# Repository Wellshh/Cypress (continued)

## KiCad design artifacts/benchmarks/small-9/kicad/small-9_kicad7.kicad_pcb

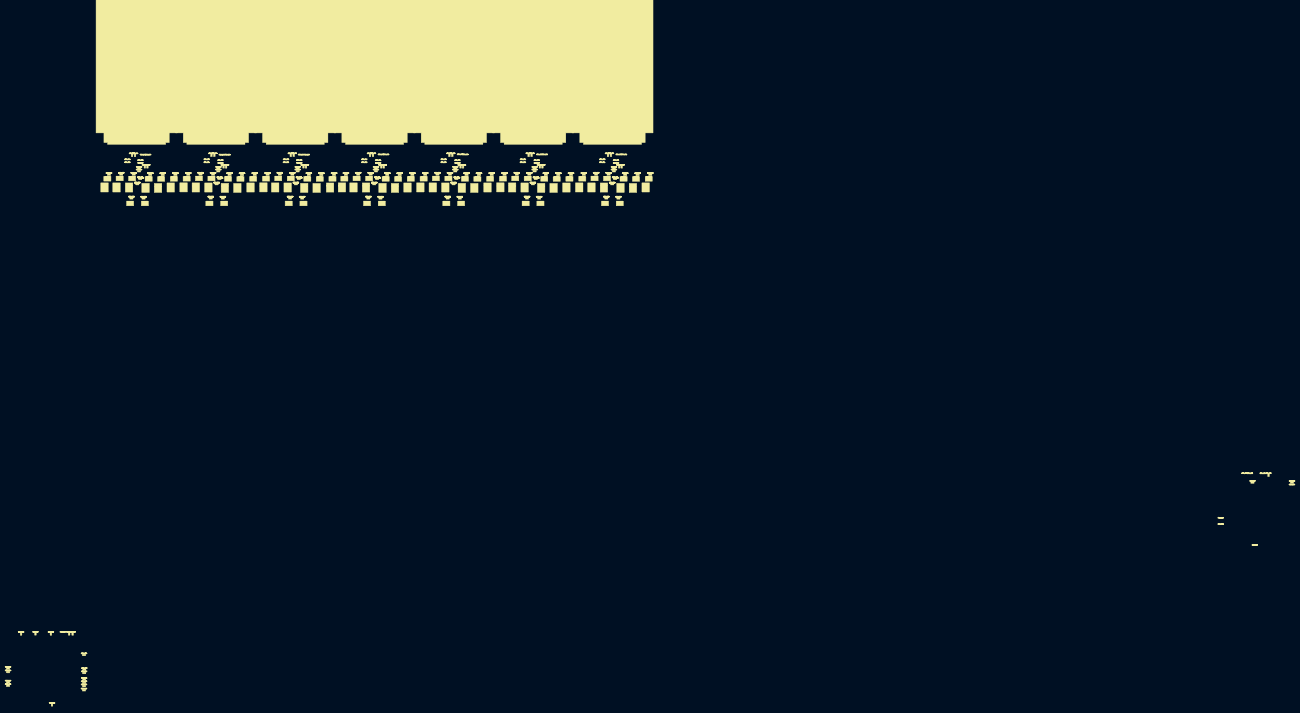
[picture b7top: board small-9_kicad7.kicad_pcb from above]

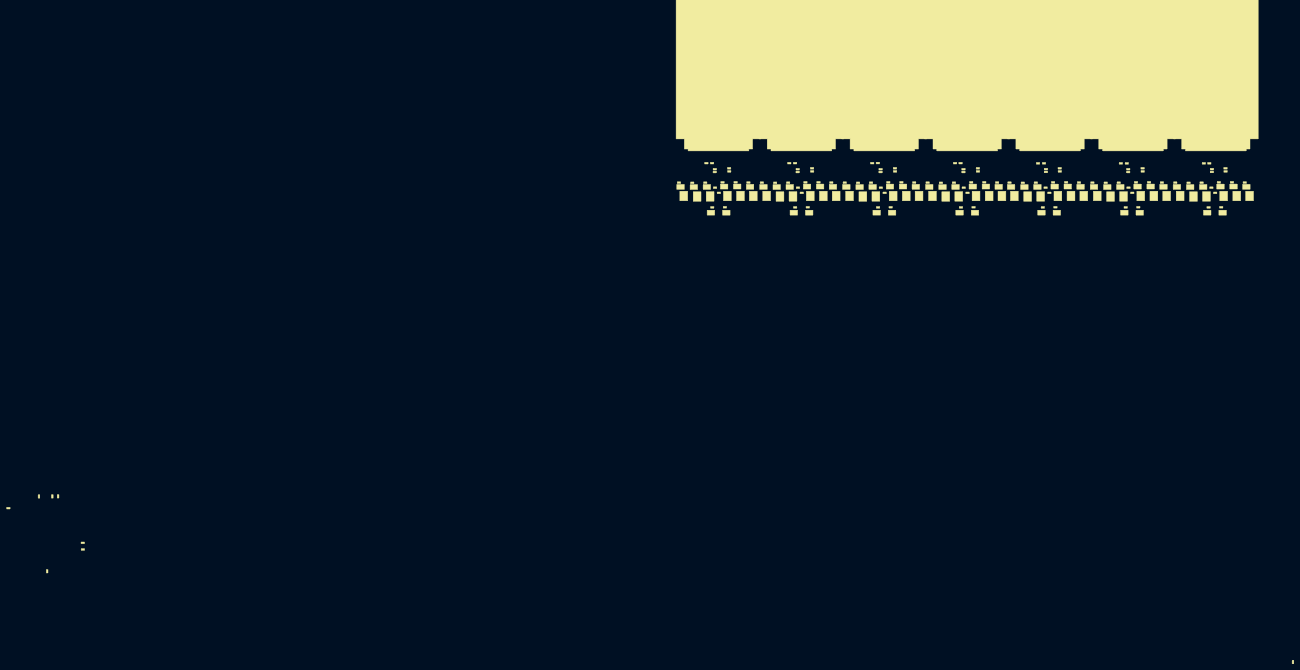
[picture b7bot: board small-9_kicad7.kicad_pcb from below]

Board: 2 copper layers, 476 parts (232 on the bottom side), 253 nets, no tracks yet.

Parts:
COMP_232: COMP_232; 320-2241-000
COMP_233: COMP_233; 320-2241-000
COMP_234: COMP_234; 320-2241-000
COMP_235: COMP_235; 320-2241-000
COMP_236: COMP_236; 320-2241-000
COMP_237: COMP_237; 320-2241-000
COMP_238: COMP_238; 320-2241-000
COMP_239: COMP_239; 320-2241-000
COMP_240: COMP_240; 320-2241-000
COMP_241: COMP_241; 320-2241-000
COMP_242: COMP_242; 320-2241-000
COMP_243: COMP_243; 320-2241-000
COMP_244: COMP_244; 320-2241-000
COMP_245: COMP_245; 320-2241-000
COMP_469: COMP_469; 032-2145-000
COMP_470: COMP_470; 032-2145-000
COMP_480: COMP_480; 032-2145-000
COMP_481: COMP_481; 032-2145-000
COMP_482: COMP_482; 032-2145-000
COMP_483: COMP_483; 032-2145-000
COMP_484: COMP_484; 032-2145-000
COMP_485: COMP_485; 032-2145-000
COMP_486: COMP_486; 032-2145-000
COMP_487: COMP_487; 032-2145-000
COMP_488: COMP_488; 032-2145-000
COMP_489: COMP_489; 032-2145-000
COMP_490: COMP_490; 032-2145-000
COMP_491: COMP_491; 032-2145-000
COMP_492: COMP_492; 032-2145-000
COMP_493: COMP_493; 032-2145-000
COMP_494: COMP_494; 032-2145-000
COMP_495: COMP_495; 032-2145-000
COMP_496: COMP_496; 032-2145-000
COMP_497: COMP_497; 032-2145-000
COMP_498: COMP_498; 032-2145-000
COMP_606: COMP_606; 032-2145-000
COMP_607: COMP_607; 032-2145-000
COMP_608: COMP_608; 032-2145-000
COMP_609: COMP_609; 032-2145-000
COMP_610: COMP_610; 032-2145-000
COMP_611: COMP_611; 032-2145-000
COMP_612: COMP_612; 032-2145-000
COMP_613: COMP_613; 032-2145-000
COMP_614: COMP_614; 032-2145-000
COMP_615: COMP_615; 032-2145-000
COMP_616: COMP_616; 032-2145-000
COMP_617: COMP_617; 032-2145-000
COMP_618: COMP_618; 032-2145-000
COMP_619: COMP_619; 032-2145-000
COMP_620: COMP_620; 032-2145-000
COMP_621: COMP_621; 032-2145-000
COMP_622: COMP_622; 032-2145-000
COMP_623: COMP_623; 032-2145-000
COMP_624: COMP_624; 032-2145-000
COMP_625: COMP_625; 032-2145-000
COMP_626: COMP_626; 032-2145-000
COMP_627: COMP_627; 032-2145-000
COMP_628: COMP_628; 032-2145-000
COMP_629: COMP_629; 032-2145-000
COMP_630: COMP_630; 032-2145-000
COMP_631: COMP_631; 032-2145-000
COMP_632: COMP_632; 032-2145-000
COMP_633: COMP_633; 032-2145-000
COMP_634: COMP_634; 032-2145-000
COMP_635: COMP_635; 032-2145-000
COMP_636: COMP_636; 032-2145-000
COMP_637: COMP_637; 032-2145-000
COMP_638: COMP_638; 032-2145-000
COMP_639: COMP_639; 032-2145-000
COMP_640: COMP_640; 032-2145-000
COMP_641: COMP_641; 032-2145-000
COMP_642: COMP_642; 032-2145-000
COMP_643: COMP_643; 032-2145-000
COMP_644: COMP_644; 032-2145-000
COMP_645: COMP_645; 032-2145-000
COMP_646: COMP_646; 032-2145-000
COMP_647: COMP_647; 032-2145-000
COMP_648: COMP_648; 032-2145-000
COMP_649: COMP_649; 032-2145-000
COMP_650: COMP_650; 032-2145-000
COMP_651: COMP_651; 032-2145-000
COMP_652: COMP_652; 032-2145-000
COMP_653: COMP_653; 032-2145-000
COMP_654: COMP_654; 032-2145-000
COMP_655: COMP_655; 032-2145-000
COMP_656: COMP_656; 032-2145-000
COMP_657: COMP_657; 032-2145-000
COMP_658: COMP_658; 032-2145-000
COMP_659: COMP_659; 032-2145-000
COMP_660: COMP_660; 032-2145-000
COMP_661: COMP_661; 032-2145-000
COMP_662: COMP_662; 032-2145-000
COMP_663: COMP_663; 032-2145-000
COMP_664: COMP_664; 032-2145-000
COMP_665: COMP_665; 032-2145-000
COMP_666: COMP_666; 032-2145-000
COMP_667: COMP_667; 032-2145-000
COMP_668: COMP_668; 032-2145-000
COMP_669: COMP_669; 032-2145-000
COMP_670: COMP_670; 032-2145-000
COMP_671: COMP_671; 032-2145-000
COMP_672: COMP_672; 032-2145-000
COMP_673: COMP_673; 032-2145-000
COMP_674: COMP_674; 032-2145-000
COMP_675: COMP_675; 032-2145-000
COMP_676: COMP_676; 032-2145-000
COMP_677: COMP_677; 032-2145-000
COMP_678: COMP_678; 032-2145-000
COMP_679: COMP_679; 032-2145-000
COMP_680: COMP_680; 032-2145-000
COMP_681: COMP_681; 032-2145-000
COMP_682: COMP_682; 032-2145-000
COMP_683: COMP_683; 032-2145-000
COMP_684: COMP_684; 032-2145-000
COMP_685: COMP_685; 032-2145-000
COMP_686: COMP_686; 032-2145-000
COMP_687: COMP_687; 032-2145-000
COMP_688: COMP_688; 032-2145-000
COMP_689: COMP_689; 032-2145-000
COMP_690: COMP_690; 032-2145-000
COMP_691: COMP_691; 032-2145-000
COMP_692: COMP_692; 032-2145-000
COMP_717: COMP_717; 032-2145-000
COMP_724: COMP_724; 032-2145-000
COMP_725: COMP_725; 032-2145-000
COMP_726: COMP_726; 032-2145-000
COMP_984: COMP_984; 080-2248-000
COMP_985: COMP_985; 080-2248-000
COMP_988: COMP_988; 080-2248-000
COMP_989: COMP_989; 080-2248-000
COMP_990: COMP_990; 080-2248-000
COMP_991: COMP_991; 080-2248-000
COMP_992: COMP_992; 080-2248-000
COMP_993: COMP_993; 080-2248-000
COMP_994: COMP_994; 080-2248-000
COMP_995: COMP_995; 080-2248-000
COMP_996: COMP_996; 080-2248-000
COMP_997: COMP_997; 080-2248-000
COMP_998: COMP_998; 080-2248-000
COMP_999: COMP_999; 080-2248-000
COMP_1016: COMP_1016; 130-1487-000
COMP_1017: COMP_1017; 130-1487-000
COMP_1102: COMP_1102; 130-1487-000
COMP_1103: COMP_1103; 130-1487-000
COMP_1104: COMP_1104; 130-1487-000
COMP_1105: COMP_1105; 130-1487-000
COMP_1106: COMP_1106; 130-1487-000
COMP_1107: COMP_1107; 130-1487-000
COMP_1108: COMP_1108; 130-1487-000
COMP_1109: COMP_1109; 130-1487-000
COMP_1110: COMP_1110; 130-1487-000
COMP_1111: COMP_1111; 130-1487-000
COMP_1112: COMP_1112; 130-1487-000
COMP_1113: COMP_1113; 130-1487-000
COMP_1114: COMP_1114; 130-1487-000
COMP_1115: COMP_1115; 130-1487-000
COMP_1116: COMP_1116; 130-1487-000
COMP_1117: COMP_1117; 130-1487-000
COMP_1118: COMP_1118; 130-1487-000
COMP_1119: COMP_1119; 130-1487-000
COMP_1120: COMP_1120; 130-1487-000
COMP_1121: COMP_1121; 130-1487-000
COMP_1122: COMP_1122; 130-1487-000
COMP_1123: COMP_1123; 130-1487-000
COMP_1124: COMP_1124; 130-1487-000
COMP_1125: COMP_1125; 130-1487-000
COMP_1126: COMP_1126; 130-1487-000
COMP_1127: COMP_1127; 130-1487-000
COMP_1128: COMP_1128; 130-1487-000
COMP_1129: COMP_1129; 130-1487-000
COMP_1130: COMP_1130; 130-1487-000
COMP_1131: COMP_1131; 130-1487-000
COMP_1132: COMP_1132; 130-1487-000
COMP_1133: COMP_1133; 130-1487-000
COMP_1134: COMP_1134; 130-1487-000
COMP_1135: COMP_1135; 130-1487-000
COMP_1136: COMP_1136; 130-1487-000
COMP_1137: COMP_1137; 130-1487-000
COMP_1138: COMP_1138; 130-1487-000
COMP_1139: COMP_1139; 130-1487-000
COMP_1140: COMP_1140; 130-1487-000
COMP_1141: COMP_1141; 130-1487-000
COMP_1142: COMP_1142; 130-1487-000
COMP_1143: COMP_1143; 130-1487-000
COMP_1144: COMP_1144; 130-1487-000
COMP_1145: COMP_1145; 130-1487-000
COMP_1146: COMP_1146; 130-1487-000
COMP_1147: COMP_1147; 130-1487-000
COMP_1148: COMP_1148; 130-1487-000
COMP_1149: COMP_1149; 130-1487-000
COMP_1150: COMP_1150; 130-1487-000
COMP_1151: COMP_1151; 130-1487-000
COMP_1152: COMP_1152; 130-1487-000
COMP_1153: COMP_1153; 130-1487-000
COMP_1154: COMP_1154; 130-1487-000
COMP_1155: COMP_1155; 130-1487-000
COMP_1156: COMP_1156; 130-1487-000
COMP_1157: COMP_1157; 130-1487-000
COMP_1158: COMP_1158; 130-1487-000
COMP_1159: COMP_1159; 130-1487-000
COMP_1160: COMP_1160; 130-1487-000
COMP_1161: COMP_1161; 130-1487-000
COMP_1162: COMP_1162; 130-1487-000
COMP_1163: COMP_1163; 130-1487-000
COMP_1164: COMP_1164; 130-1487-000
COMP_1165: COMP_1165; 130-1487-000
COMP_1166: COMP_1166; 130-1487-000
COMP_1167: COMP_1167; 130-1487-000
COMP_1168: COMP_1168; 130-1487-000
COMP_1169: COMP_1169; 130-1487-000
COMP_1170: COMP_1170; 130-1487-000
COMP_1171: COMP_1171; 130-1487-000
COMP_1172: COMP_1172; 130-1487-000
COMP_1173: COMP_1173; 130-1487-000
COMP_1174: COMP_1174; 130-1487-000
COMP_1175: COMP_1175; 130-1487-000
COMP_1176: COMP_1176; 130-1487-000
COMP_1177: COMP_1177; 130-1487-000
COMP_1178: COMP_1178; 130-1487-000
COMP_1179: COMP_1179; 130-1487-000
COMP_1180: COMP_1180; 130-1487-000
COMP_1202: COMP_1202; 130-1487-000
COMP_1203: COMP_1203; 130-1487-000
COMP_1204: COMP_1204; 130-1487-000
COMP_2407: COMP_2407; 032-0863-000
COMP_2473: COMP_2473; 195-0004-000
COMP_2474: COMP_2474; 195-0004-000
COMP_2475: COMP_2475; 195-0004-000
COMP_2477: COMP_2477; 195-0004-000
COMP_2478: COMP_2478; 195-0004-000
COMP_2479: COMP_2479; 195-0004-000
COMP_2480: COMP_2480; 195-0004-000
COMP_2481: COMP_2481; 195-0004-000
COMP_2482: COMP_2482; 195-0004-000
COMP_2483: COMP_2483; 195-0004-000
COMP_2484: COMP_2484; 195-0004-000
COMP_2485: COMP_2485; 195-0004-000
COMP_2486: COMP_2486; 195-0004-000
COMP_2487: COMP_2487; 195-0004-000
COMP_2488: COMP_2488; 195-0004-000
COMP_2489: COMP_2489; 195-0004-000
COMP_2490: COMP_2490; 195-0004-000
COMP_2491: COMP_2491; 195-0004-000
COMP_2492: COMP_2492; 195-0004-000
COMP_2493: COMP_2493; 195-0004-000
COMP_2494: COMP_2494; 195-0004-000
COMP_2495: COMP_2495; 195-0004-000
COMP_2496: COMP_2496; 195-0004-000
COMP_2497: COMP_2497; 195-0004-000
COMP_2498: COMP_2498; 195-0004-000
COMP_2499: COMP_2499; 195-0004-000
COMP_2500: COMP_2500; 195-0004-000
COMP_2501: COMP_2501; 195-0004-000
COMP_2502: COMP_2502; 195-0004-000
COMP_2503: COMP_2503; 195-0004-000
COMP_2504: COMP_2504; 195-0004-000
COMP_2505: COMP_2505; 195-0004-000
COMP_2506: COMP_2506; 195-0004-000
COMP_2507: COMP_2507; 195-0004-000
COMP_2508: COMP_2508; 195-0004-000
COMP_2509: COMP_2509; 195-0004-000
COMP_2510: COMP_2510; 195-0004-000
COMP_2511: COMP_2511; 195-0004-000
COMP_2512: COMP_2512; 195-0004-000
COMP_2513: COMP_2513; 195-0004-000
COMP_2514: COMP_2514; 195-0004-000
COMP_2515: COMP_2515; 195-0004-000
COMP_2516: COMP_2516; 195-0004-000
COMP_2517: COMP_2517; 195-0004-000
COMP_2518: COMP_2518; 195-0004-000
COMP_2519: COMP_2519; 195-0004-000
COMP_2520: COMP_2520; 195-0004-000
COMP_2521: COMP_2521; 195-0004-000
COMP_2522: COMP_2522; 195-0004-000
COMP_2523: COMP_2523; 195-0004-000
COMP_2524: COMP_2524; 195-0004-000
COMP_2525: COMP_2525; 195-0004-000
COMP_2526: COMP_2526; 195-0004-000
COMP_2544: COMP_2544; 195-0004-000
COMP_2545: COMP_2545; 195-0004-000
COMP_2548: COMP_2548; 195-0004-000
COMP_2590: COMP_2590; 195-0005-000
COMP_2591: COMP_2591; 195-0005-000
COMP_2592: COMP_2592; 195-0005-000
COMP_2593: COMP_2593; 195-0005-000
COMP_2594: COMP_2594; 195-0005-000
COMP_2595: COMP_2595; 195-0005-000
COMP_2596: COMP_2596; 195-0005-000
COMP_2597: COMP_2597; 195-0005-000
COMP_2598: COMP_2598; 195-0005-000
COMP_2599: COMP_2599; 195-0005-000
COMP_2600: COMP_2600; 195-0005-000
COMP_2601: COMP_2601; 195-0005-000
COMP_2602: COMP_2602; 195-0005-000
COMP_2603: COMP_2603; 195-0005-000
COMP_2604: COMP_2604; 195-0005-000
COMP_2605: COMP_2605; 195-0005-000
COMP_2606: COMP_2606; 195-0005-000
COMP_2607: COMP_2607; 195-0005-000
COMP_2608: COMP_2608; 195-0005-000
COMP_2609: COMP_2609; 195-0005-000
COMP_2610: COMP_2610; 195-0005-000
COMP_2611: COMP_2611; 195-0005-000
COMP_2612: COMP_2612; 195-0005-000
COMP_2613: COMP_2613; 195-0005-000
COMP_2614: COMP_2614; 195-0005-000
COMP_2615: COMP_2615; 195-0005-000
COMP_2616: COMP_2616; 195-0005-000
COMP_2617: COMP_2617; 195-0005-000
COMP_2618: COMP_2618; 195-0005-000
COMP_2619: COMP_2619; 195-0005-000
COMP_2620: COMP_2620; 195-0005-000
COMP_2621: COMP_2621; 195-0005-000
COMP_2622: COMP_2622; 195-0005-000
COMP_2623: COMP_2623; 195-0005-000
COMP_2624: COMP_2624; 195-0005-000
COMP_2625: COMP_2625; 195-0005-000
COMP_2626: COMP_2626; 195-0005-000
COMP_2627: COMP_2627; 195-0005-000
COMP_2628: COMP_2628; 195-0005-000
COMP_2629: COMP_2629; 195-0005-000
COMP_2630: COMP_2630; 195-0005-000
COMP_2631: COMP_2631; 195-0005-000
COMP_2632: COMP_2632; 195-0005-000
COMP_2633: COMP_2633; 195-0005-000
COMP_2634: COMP_2634; 195-0005-000
COMP_2635: COMP_2635; 195-0005-000
COMP_2636: COMP_2636; 195-0005-000
COMP_2637: COMP_2637; 195-0005-000
COMP_2638: COMP_2638; 195-0005-000
COMP_2639: COMP_2639; 195-0005-000
COMP_2640: COMP_2640; 195-0005-000
COMP_2641: COMP_2641; 195-0005-000
COMP_2642: COMP_2642; 195-0005-000
COMP_2643: COMP_2643; 195-0005-000
COMP_2644: COMP_2644; 195-0005-000
COMP_2645: COMP_2645; 195-0005-000
COMP_2662: COMP_2662; 032-0863-000
COMP_2663: COMP_2663; 032-0863-000
COMP_2664: COMP_2664; 032-0863-000
COMP_2665: COMP_2665; 032-0863-000
COMP_2666: COMP_2666; 032-0863-000
COMP_2667: COMP_2667; 032-0863-000
COMP_2668: COMP_2668; 032-0863-000
COMP_2669: COMP_2669; 032-0863-000
COMP_2670: COMP_2670; 032-0863-000
COMP_2671: COMP_2671; 032-0863-000
COMP_2672: COMP_2672; 032-0863-000
COMP_2673: COMP_2673; 032-0863-000
COMP_2676: COMP_2676; 032-0863-000
COMP_2677: COMP_2677; 032-0863-000
COMP_2678: COMP_2678; 032-0863-000
COMP_2688: COMP_2688; 032-0863-000
COMP_2794: COMP_2794; 032-0863-000
COMP_2795: COMP_2795; 032-0863-000
COMP_2796: COMP_2796; 032-0863-000
COMP_2797: COMP_2797; 032-0863-000
COMP_2798: COMP_2798; 032-0863-000
COMP_2799: COMP_2799; 032-0863-000
COMP_2800: COMP_2800; 032-0863-000
COMP_2801: COMP_2801; 032-0863-000
COMP_2802: COMP_2802; 032-0863-000
COMP_2803: COMP_2803; 032-0863-000
COMP_2804: COMP_2804; 032-0863-000
COMP_2805: COMP_2805; 032-0863-000
COMP_2806: COMP_2806; 032-0863-000
COMP_2807: COMP_2807; 032-0863-000
COMP_2808: COMP_2808; 032-0863-000
COMP_2809: COMP_2809; 032-0863-000
COMP_2810: COMP_2810; 032-0863-000
COMP_2811: COMP_2811; 032-0863-000
COMP_2812: COMP_2812; 032-0863-000
COMP_2813: COMP_2813; 032-0863-000
COMP_2814: COMP_2814; 032-0863-000
COMP_2815: COMP_2815; 032-0863-000
COMP_2816: COMP_2816; 032-0863-000
COMP_2817: COMP_2817; 032-0863-000
COMP_2818: COMP_2818; 032-0863-000
COMP_2819: COMP_2819; 032-0863-000
COMP_2820: COMP_2820; 032-0863-000
COMP_2821: COMP_2821; 032-0863-000
COMP_2822: COMP_2822; 032-0863-000
COMP_2823: COMP_2823; 032-0863-000
COMP_2824: COMP_2824; 032-0863-000
COMP_2825: COMP_2825; 032-0863-000
COMP_2826: COMP_2826; 032-0863-000
COMP_2827: COMP_2827; 032-0863-000
COMP_2828: COMP_2828; 032-0863-000
COMP_2829: COMP_2829; 032-0863-000
COMP_2830: COMP_2830; 032-0863-000
COMP_2831: COMP_2831; 032-0863-000
COMP_2832: COMP_2832; 032-0863-000
COMP_2833: COMP_2833; 032-0863-000
COMP_2834: COMP_2834; 032-0863-000
COMP_2835: COMP_2835; 032-0863-000
COMP_2836: COMP_2836; 032-0863-000
COMP_2837: COMP_2837; 032-0863-000
COMP_2838: COMP_2838; 032-0863-000
COMP_2839: COMP_2839; 032-0863-000
COMP_2840: COMP_2840; 032-0863-000
COMP_2841: COMP_2841; 032-0863-000
COMP_2842: COMP_2842; 032-0863-000
COMP_2843: COMP_2843; 032-0863-000
COMP_2844: COMP_2844; 032-0863-000
COMP_2845: COMP_2845; 032-0863-000
COMP_2846: COMP_2846; 032-0863-000
COMP_2847: COMP_2847; 032-0863-000
COMP_2848: COMP_2848; 032-0863-000
COMP_2849: COMP_2849; 032-0863-000
COMP_2850: COMP_2850; 032-0863-000
COMP_2851: COMP_2851; 032-0863-000
COMP_2852: COMP_2852; 032-0863-000
COMP_2853: COMP_2853; 032-0863-000
COMP_2854: COMP_2854; 032-0863-000
COMP_2855: COMP_2855; 032-0863-000
COMP_2856: COMP_2856; 032-0863-000
COMP_2857: COMP_2857; 032-0863-000
COMP_2858: COMP_2858; 032-0863-000
COMP_2859: COMP_2859; 032-0863-000
COMP_2860: COMP_2860; 032-0863-000
COMP_2861: COMP_2861; 032-0863-000
COMP_2862: COMP_2862; 032-0863-000
COMP_2863: COMP_2863; 032-0863-000
COMP_2864: COMP_2864; 032-0863-000
COMP_2865: COMP_2865; 032-0863-000
COMP_2866: COMP_2866; 032-0863-000
COMP_2867: COMP_2867; 032-0863-000
COMP_2868: COMP_2868; 032-0863-000
COMP_2869: COMP_2869; 032-0863-000
COMP_2870: COMP_2870; 032-0863-000
COMP_2871: COMP_2871; 032-0863-000
COMP_2872: COMP_2872; 032-0863-000
COMP_2873: COMP_2873; 032-0863-000
COMP_2874: COMP_2874; 032-0863-000
COMP_2875: COMP_2875; 032-0863-000
COMP_2876: COMP_2876; 032-0863-000
COMP_2877: COMP_2877; 032-0863-000
COMP_2878: COMP_2878; 032-0863-000
COMP_2879: COMP_2879; 032-0863-000
COMP_2880: COMP_2880; 032-0863-000
COMP_2881: COMP_2881; 032-0863-000
COMP_2882: COMP_2882; 032-0863-000
COMP_2883: COMP_2883; 032-0863-000
COMP_2951: COMP_2951; 195-0337-000
COMP_2952: COMP_2952; 195-0337-000
COMP_2953: COMP_2953; 195-0337-000
COMP_2954: COMP_2954; 195-0337-000
COMP_2955: COMP_2955; 195-0337-000
COMP_2956: COMP_2956; 195-0337-000
COMP_2957: COMP_2957; 195-0337-000
COMP_2958: COMP_2958; 195-0337-000
COMP_2959: COMP_2959; 195-0337-000
COMP_2960: COMP_2960; 195-0337-000
COMP_2961: COMP_2961; 195-0337-000
COMP_2962: COMP_2962; 195-0337-000
COMP_2963: COMP_2963; 195-0337-000
COMP_2964: COMP_2964; 195-0337-000
COMP_2965: COMP_2965; 195-0337-000
COMP_2966: COMP_2966; 195-0337-000
COMP_2967: COMP_2967; 195-0337-000
COMP_2968: COMP_2968; 195-0337-000
COMP_2969: COMP_2969; 195-0337-000
COMP_2970: COMP_2970; 195-0337-000
COMP_2971: COMP_2971; 195-0337-000
COMP_2972: COMP_2972; 195-0337-000
COMP_2973: COMP_2973; 195-0337-000
COMP_2974: COMP_2974; 195-0337-000
COMP_2975: COMP_2975; 195-0337-000
COMP_2976: COMP_2976; 195-0337-000
COMP_2977: COMP_2977; 195-0337-000
COMP_2978: COMP_2978; 195-0337-000
COMP_2983: COMP_2983; 032-0863-000
COMP_3006: COMP_3006; 032-0863-000
COMP_3007: COMP_3007; 032-0863-000
COMP_3008: COMP_3008; 032-0863-000
COMP_3009: COMP_3009; 032-0863-000

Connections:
NET_28: COMP_685.1, COMP_988.T30, COMP_988.T68, COMP_1175.2, COMP_2523.1, COMP_2642.1, COMP_2644.1, COMP_2876.1
NET_29: COMP_688.1, COMP_988.B30, COMP_988.B68, COMP_1178.2, COMP_2524.1, COMP_2643.1, COMP_2645.1, COMP_2879.1
NET_30: COMP_680.1, COMP_989.B30, COMP_989.B68, COMP_1172.2, COMP_2520.1, COMP_2639.1, COMP_2641.1, COMP_2871.1
NET_31: COMP_677.1, COMP_989.T30, COMP_989.T68, COMP_1169.2, COMP_2519.1, COMP_2638.1, COMP_2640.1, COMP_2868.1
NET_32: COMP_669.1, COMP_990.T30, COMP_990.T68, COMP_1163.2, COMP_2515.1, COMP_2634.1, COMP_2636.1, COMP_2860.1
NET_33: COMP_672.1, COMP_990.B30, COMP_990.B68, COMP_1166.2, COMP_2516.1, COMP_2635.1, COMP_2637.1, COMP_2863.1
NET_34: COMP_664.1, COMP_991.B30, COMP_991.B68, COMP_1160.2, COMP_2512.1, COMP_2631.1, COMP_2633.1, COMP_2855.1
NET_35: COMP_661.1, COMP_991.T30, COMP_991.T68, COMP_1157.2, COMP_2511.1, COMP_2630.1, COMP_2632.1, COMP_2852.1
NET_36: COMP_496.1, COMP_985.T30, COMP_985.T68, COMP_1154.2, COMP_2507.1, COMP_2626.1, COMP_2628.1, COMP_2983.1
NET_37: COMP_726.1, COMP_985.B30, COMP_985.B68, COMP_1202.2, COMP_2508.1, COMP_2627.1, COMP_2629.1, COMP_3006.1
NET_38: COMP_491.1, COMP_992.B30, COMP_992.B68, COMP_1151.2, COMP_2504.1, COMP_2623.1, COMP_2625.1, COMP_2670.1
NET_39: COMP_488.1, COMP_992.T30, COMP_992.T68, COMP_1148.2, COMP_2503.1, COMP_2622.1, COMP_2624.1, COMP_2667.1
NET_40: COMP_656.1, COMP_984.T30, COMP_984.T68, COMP_1142.2, COMP_2499.1, COMP_2618.1, COMP_2620.1, COMP_2846.1
NET_41: COMP_659.1, COMP_984.B30, COMP_984.B68, COMP_1145.2, COMP_2500.1, COMP_2619.1, COMP_2621.1, COMP_2849.1
NET_42: COMP_651.1, COMP_993.B30, COMP_993.B68, COMP_1139.2, COMP_2496.1, COMP_2615.1, COMP_2617.1, COMP_2841.1
NET_43: COMP_648.1, COMP_993.T30, COMP_993.T68, COMP_1016.2, COMP_2495.1, COMP_2614.1, COMP_2616.1, COMP_2838.1
NET_44: COMP_640.1, COMP_994.T30, COMP_994.T68, COMP_1132.2, COMP_2491.1, COMP_2610.1, COMP_2612.1, COMP_2830.1
NET_45: COMP_643.1, COMP_994.B30, COMP_994.B68, COMP_1135.2, COMP_2492.1, COMP_2611.1, COMP_2613.1, COMP_2833.1
NET_46: COMP_635.1, COMP_995.B30, COMP_995.B68, COMP_1129.2, COMP_2488.1, COMP_2607.1, COMP_2609.1, COMP_2825.1
NET_47: COMP_632.1, COMP_995.T30, COMP_995.T68, COMP_1126.2, COMP_2487.1, COMP_2606.1, COMP_2608.1, COMP_2822.1
NET_48: COMP_483.1, COMP_996.T30, COMP_996.T68, COMP_1120.2, COMP_2483.1, COMP_2602.1, COMP_2604.1, COMP_2815.1
NET_49: COMP_627.1, COMP_996.B30, COMP_996.B68, COMP_1123.2, COMP_2484.1, COMP_2603.1, COMP_2605.1, COMP_2664.1
NET_50: COMP_481.1, COMP_997.B30, COMP_997.B68, COMP_1117.2, COMP_2480.1, COMP_2599.1, COMP_2601.1, COMP_2662.1
NET_51: COMP_620.1, COMP_997.T30, COMP_997.T68, COMP_1114.2, COMP_2479.1, COMP_2598.1, COMP_2600.1, COMP_2809.1
NET_52: COMP_614.1, COMP_998.T30, COMP_998.T68, COMP_1108.2, COMP_2544.1, COMP_2594.1, COMP_2596.1, COMP_2802.1
NET_53: COMP_617.1, COMP_998.B30, COMP_998.B68, COMP_1111.2, COMP_2545.1, COMP_2595.1, COMP_2597.1, COMP_2805.1
NET_54: COMP_609.1, COMP_999.B30, COMP_999.B68, COMP_1105.2, COMP_2474.1, COMP_2591.1, COMP_2593.1, COMP_2797.1
NET_55: COMP_606.1, COMP_999.T30, COMP_999.T68, COMP_1102.2, COMP_2473.1, COMP_2590.1, COMP_2592.1, COMP_2794.1
NET_92: COMP_687.1, COMP_988.T10, COMP_988.T48, COMP_1177.2, COMP_2878.1
NET_93: COMP_690.1, COMP_988.B10, COMP_988.B48, COMP_1180.2, COMP_2881.1
NET_94: COMP_682.1, COMP_989.B10, COMP_989.B48, COMP_1174.2, COMP_2873.1
NET_95: COMP_679.1, COMP_989.T10, COMP_989.T48, COMP_1171.2, COMP_2870.1
NET_96: COMP_671.1, COMP_990.T10, COMP_990.T48, COMP_1165.2, COMP_2862.1
NET_97: COMP_674.1, COMP_990.B10, COMP_990.B48, COMP_1168.2, COMP_2865.1
NET_98: COMP_666.1, COMP_991.B10, COMP_991.B48, COMP_1162.2, COMP_2857.1
NET_99: COMP_663.1, COMP_991.T10, COMP_991.T48, COMP_1159.2, COMP_2854.1
NET_100: COMP_498.1, COMP_985.T10, COMP_985.T48, COMP_1156.2, COMP_2677.1
NET_101: COMP_724.1, COMP_985.B10, COMP_985.B48, COMP_1204.2, COMP_3009.1
NET_102: COMP_493.1, COMP_992.B10, COMP_992.B48, COMP_1153.2, COMP_2672.1
NET_103: COMP_490.1, COMP_992.T10, COMP_992.T48, COMP_1150.2, COMP_2669.1
NET_104: COMP_658.1, COMP_984.T10, COMP_984.T48, COMP_1144.2, COMP_2848.1
NET_105: COMP_485.1, COMP_984.B10, COMP_984.B48, COMP_1147.2, COMP_2851.1
NET_106: COMP_653.1, COMP_993.B10, COMP_993.B48, COMP_1141.2, COMP_2843.1
NET_107: COMP_650.1, COMP_993.T10, COMP_993.T48, COMP_1138.2, COMP_2840.1
NET_108: COMP_642.1, COMP_994.T10, COMP_994.T48, COMP_1134.2, COMP_2832.1
NET_109: COMP_645.1, COMP_994.B10, COMP_994.B48, COMP_1137.2, COMP_2835.1
NET_110: COMP_637.1, COMP_995.B10, COMP_995.B48, COMP_1131.2, COMP_2827.1
NET_111: COMP_634.1, COMP_995.T10, COMP_995.T48, COMP_1128.2, COMP_2824.1
NET_112: COMP_626.1, COMP_996.T10, COMP_996.T48, COMP_1122.2, COMP_2817.1
NET_113: COMP_629.1, COMP_996.B10, COMP_996.B48, COMP_1125.2, COMP_2819.1
NET_114: COMP_482.1, COMP_997.B10, COMP_997.B48, COMP_1119.2, COMP_2663.1
NET_115: COMP_621.1, COMP_997.T10, COMP_997.T48, COMP_1116.2, COMP_2811.1
NET_116: COMP_616.1, COMP_998.T10, COMP_998.T48, COMP_1110.2, COMP_2804.1
NET_117: COMP_469.1, COMP_998.B10, COMP_998.B48, COMP_1113.2, COMP_2407.1
NET_118: COMP_611.1, COMP_999.B10, COMP_999.B48, COMP_1107.2, COMP_2799.1
NET_119: COMP_608.1, COMP_999.T10, COMP_999.T48, COMP_1104.2, COMP_2796.1
NET_156: COMP_686.1, COMP_988.T29, COMP_988.T67, COMP_1176.2, COMP_2877.1
NET_157: COMP_689.1, COMP_988.B29, COMP_988.B67, COMP_1179.2, COMP_2880.1
NET_158: COMP_681.1, COMP_989.B29, COMP_989.B67, COMP_1173.2, COMP_2872.1
NET_159: COMP_678.1, COMP_989.T29, COMP_989.T67, COMP_1170.2, COMP_2869.1
NET_160: COMP_670.1, COMP_990.T29, COMP_990.T67, COMP_1164.2, COMP_2861.1
NET_161: COMP_673.1, COMP_990.B29, COMP_990.B67, COMP_1167.2, COMP_2864.1
NET_162: COMP_665.1, COMP_991.B29, COMP_991.B67, COMP_1161.2, COMP_2856.1
NET_163: COMP_662.1, COMP_991.T29, COMP_991.T67, COMP_1158.2, COMP_2853.1
NET_164: COMP_497.1, COMP_985.T29, COMP_985.T67, COMP_1155.2, COMP_2676.1
NET_165: COMP_725.1, COMP_985.B29, COMP_985.B67, COMP_1203.2, COMP_3008.1
NET_166: COMP_492.1, COMP_992.B29, COMP_992.B67, COMP_1152.2, COMP_2671.1
NET_167: COMP_489.1, COMP_992.T29, COMP_992.T67, COMP_1149.2, COMP_2668.1
NET_168: COMP_657.1, COMP_984.T29, COMP_984.T67, COMP_1143.2, COMP_2847.1
NET_169: COMP_484.1, COMP_984.B29, COMP_984.B67, COMP_1146.2, COMP_2850.1
NET_170: COMP_652.1, COMP_993.B29, COMP_993.B67, COMP_1140.2, COMP_2842.1
NET_171: COMP_649.1, COMP_993.T29, COMP_993.T67, COMP_1017.2, COMP_2839.1
NET_172: COMP_641.1, COMP_994.T29, COMP_994.T67, COMP_1133.2, COMP_2831.1
NET_173: COMP_644.1, COMP_994.B29, COMP_994.B67, COMP_1136.2, COMP_2834.1
NET_174: COMP_636.1, COMP_995.B29, COMP_995.B67, COMP_1130.2, COMP_2826.1
NET_175: COMP_633.1, COMP_995.T29, COMP_995.T67, COMP_1127.2, COMP_2823.1
NET_176: COMP_625.1, COMP_996.T29, COMP_996.T67, COMP_1121.2, COMP_2816.1
NET_177: COMP_628.1, COMP_996.B29, COMP_996.B67, COMP_1124.2, COMP_2818.1
NET_178: COMP_622.1, COMP_997.B29, COMP_997.B67, COMP_1118.2, COMP_2812.1
NET_179: COMP_480.1, COMP_997.T29, COMP_997.T67, COMP_1115.2, COMP_2810.1
NET_180: COMP_615.1, COMP_998.T29, COMP_998.T67, COMP_1109.2, COMP_2803.1
NET_181: COMP_618.1, COMP_998.B29, COMP_998.B67, COMP_1112.2, COMP_2806.1
NET_182: COMP_610.1, COMP_999.B29, COMP_999.B67, COMP_1106.2, COMP_2798.1
NET_183: COMP_607.1, COMP_999.T29, COMP_999.T67, COMP_1103.2, COMP_2795.1
NET_218: COMP_2475.1, COMP_2477.1, COMP_2478.1, COMP_2481.1, COMP_2482.1, COMP_2485.1, COMP_2486.1, COMP_2489.1, COMP_2490.1, COMP_2493.1, COMP_2494.1, COMP_2497.1, COMP_2498.1, COMP_2501.1, COMP_2502.1, COMP_2505.1, COMP_2506.1, COMP_2509.1, COMP_2510.1, COMP_2513.1, COMP_2514.1, COMP_2517.1, COMP_2518.1, COMP_2521.1, COMP_2522.1, COMP_2525.1, COMP_2526.1, COMP_2548.1
NET_246: COMP_691.1, COMP_1175.1, COMP_1176.1, COMP_1177.1, COMP_2882.1
NET_247: COMP_692.1, COMP_1178.1, COMP_1179.1, COMP_1180.1, COMP_2883.1
NET_248: COMP_684.1, COMP_1172.1, COMP_1173.1, COMP_1174.1, COMP_2875.1
NET_249: COMP_683.1, COMP_1169.1, COMP_1170.1, COMP_1171.1, COMP_2874.1
NET_250: COMP_675.1, COMP_1163.1, COMP_1164.1, COMP_1165.1, COMP_2866.1
NET_251: COMP_676.1, COMP_1166.1, COMP_1167.1, COMP_1168.1, COMP_2867.1
NET_252: COMP_668.1, COMP_1160.1, COMP_1161.1, COMP_1162.1, COMP_2859.1
NET_253: COMP_667.1, COMP_1157.1, COMP_1158.1, COMP_1159.1, COMP_2858.1
NET_254: COMP_660.1, COMP_1154.1, COMP_1155.1, COMP_1156.1, COMP_2678.1
NET_255: COMP_717.1, COMP_1202.1, COMP_1203.1, COMP_1204.1, COMP_3007.1
NET_256: COMP_495.1, COMP_1151.1, COMP_1152.1, COMP_1153.1, COMP_2688.1
NET_257: COMP_494.1, COMP_1148.1, COMP_1149.1, COMP_1150.1, COMP_2673.1
NET_258: COMP_486.1, COMP_1142.1, COMP_1143.1, COMP_1144.1, COMP_2665.1
NET_259: COMP_487.1, COMP_1145.1, COMP_1146.1, COMP_1147.1, COMP_2666.1
NET_260: COMP_655.1, COMP_1139.1, COMP_1140.1, COMP_1141.1, COMP_2845.1
NET_261: COMP_654.1, COMP_1016.1, COMP_1017.1, COMP_1138.1, COMP_2844.1
NET_262: COMP_646.1, COMP_1132.1, COMP_1133.1, COMP_1134.1, COMP_2836.1
NET_263: COMP_647.1, COMP_1135.1, COMP_1136.1, COMP_1137.1, COMP_2837.1
NET_264: COMP_639.1, COMP_1129.1, COMP_1130.1, COMP_1131.1, COMP_2829.1
NET_265: COMP_638.1, COMP_1126.1, COMP_1127.1, COMP_1128.1, COMP_2828.1
NET_266: COMP_630.1, COMP_1120.1, COMP_1121.1, COMP_1122.1, COMP_2820.1
NET_267: COMP_631.1, COMP_1123.1, COMP_1124.1, COMP_1125.1, COMP_2821.1
NET_268: COMP_624.1, COMP_1117.1, COMP_1118.1, COMP_1119.1, COMP_2814.1
NET_269: COMP_623.1, COMP_1114.1, COMP_1115.1, COMP_1116.1, COMP_2813.1
NET_270: COMP_619.1, COMP_1108.1, COMP_1109.1, COMP_1110.1, COMP_2807.1
NET_271: COMP_470.1, COMP_1111.1, COMP_1112.1, COMP_1113.1, COMP_2808.1
NET_272: COMP_613.1, COMP_1105.1, COMP_1106.1, COMP_1107.1, COMP_2801.1
NET_273: COMP_612.1, COMP_1102.1, COMP_1103.1, COMP_1104.1, COMP_2800.1
NET_767: COMP_988.T69, COMP_2977.1
NET_768: COMP_988.B69, COMP_2978.1
NET_769: COMP_989.B69, COMP_2976.1
NET_770: COMP_989.T69, COMP_2975.1
NET_771: COMP_990.T69, COMP_2973.1
NET_772: COMP_990.B69, COMP_2974.1
NET_773: COMP_991.B69, COMP_2972.1
NET_774: COMP_991.T69, COMP_2971.1
NET_775: COMP_985.T69, COMP_2969.1
NET_776: COMP_985.B69, COMP_2970.1
NET_777: COMP_992.B69, COMP_2968.1
NET_778: COMP_992.T69, COMP_2967.1
NET_779: COMP_984.T69, COMP_2965.1
NET_780: COMP_984.B69, COMP_2966.1
NET_781: COMP_993.B69, COMP_2964.1
NET_782: COMP_993.T69, COMP_2963.1
NET_783: COMP_994.T69, COMP_2961.1
NET_784: COMP_994.B69, COMP_2962.1
NET_785: COMP_995.B69, COMP_2960.1
NET_786: COMP_995.T69, COMP_2959.1
NET_787: COMP_996.T69, COMP_2957.1
NET_788: COMP_996.B69, COMP_2958.1
NET_789: COMP_997.B69, COMP_2956.1
NET_790: COMP_997.T69, COMP_2955.1
NET_791: COMP_998.T69, COMP_2953.1
NET_792: COMP_998.B69, COMP_2954.1
NET_793: COMP_999.B69, COMP_2952.1
NET_794: COMP_999.T69, COMP_2951.1
NET_898: COMP_988.T28, COMP_2523.2
NET_899: COMP_988.B28, COMP_2524.2
NET_900: COMP_989.B28, COMP_2520.2
NET_901: COMP_989.T28, COMP_2519.2
NET_902: COMP_990.T28, COMP_2515.2
NET_903: COMP_990.B28, COMP_2516.2
NET_904: COMP_991.B28, COMP_2512.2
NET_905: COMP_991.T28, COMP_2511.2
NET_906: COMP_985.T28, COMP_2507.2
NET_907: COMP_985.B28, COMP_2508.2
NET_908: COMP_992.B28, COMP_2504.2
NET_909: COMP_992.T28, COMP_2503.2
NET_910: COMP_984.T28, COMP_2499.2
NET_911: COMP_984.B28, COMP_2500.2
NET_912: COMP_993.B28, COMP_2496.2
NET_913: COMP_993.T28, COMP_2495.2
NET_914: COMP_994.T28, COMP_2491.2
NET_915: COMP_994.B28, COMP_2492.2
NET_916: COMP_995.B28, COMP_2488.2
NET_917: COMP_995.T28, COMP_2487.2
NET_918: COMP_996.T28, COMP_2483.2
NET_919: COMP_996.B28, COMP_2484.2
NET_920: COMP_997.B28, COMP_2480.2
NET_921: COMP_997.T28, COMP_2479.2
NET_922: COMP_998.T28, COMP_2544.2
NET_923: COMP_998.B28, COMP_2545.2
NET_924: COMP_999.B28, COMP_2474.2
NET_925: COMP_999.T28, COMP_2473.2
NET_1048: COMP_988.T27, COMP_2525.2
NET_1049: COMP_988.B27, COMP_2526.2
NET_1050: COMP_989.B27, COMP_2522.2
NET_1051: COMP_989.T27, COMP_2521.2
NET_1052: COMP_990.T27, COMP_2517.2
NET_1053: COMP_990.B27, COMP_2518.2
NET_1054: COMP_991.B27, COMP_2514.2
NET_1055: COMP_991.T27, COMP_2513.2
NET_1056: COMP_985.T27, COMP_2509.2
NET_1057: COMP_985.B27, COMP_2510.2
NET_1058: COMP_992.B27, COMP_2506.2
NET_1059: COMP_992.T27, COMP_2505.2
NET_1060: COMP_984.T27, COMP_2501.2
NET_1061: COMP_984.B27, COMP_2502.2
NET_1062: COMP_993.B27, COMP_2498.2
NET_1063: COMP_993.T27, COMP_2497.2
NET_1064: COMP_994.T27, COMP_2493.2
NET_1065: COMP_994.B27, COMP_2494.2
NET_1066: COMP_995.B27, COMP_2490.2
NET_1067: COMP_995.T27, COMP_2489.2
NET_1068: COMP_996.T27, COMP_2485.2
NET_1069: COMP_996.B27, COMP_2486.2
NET_1070: COMP_997.B27, COMP_2482.2
NET_1071: COMP_997.T27, COMP_2481.2
NET_1072: COMP_998.T27, COMP_2548.2
NET_1073: COMP_998.B27, COMP_2478.2
NET_1074: COMP_999.B27, COMP_2477.2
NET_1075: COMP_999.T27, COMP_2475.2
NET_3501: COMP_988.T11, COMP_2644.2
NET_3502: COMP_988.B11, COMP_2645.2
NET_3503: COMP_989.B11, COMP_2641.2
NET_3504: COMP_989.T11, COMP_2640.2
NET_3505: COMP_990.T11, COMP_2636.2
NET_3506: COMP_990.B11, COMP_2637.2
NET_3507: COMP_991.B11, COMP_2633.2
NET_3508: COMP_991.T11, COMP_2632.2
NET_3509: COMP_985.T11, COMP_2628.2
NET_3510: COMP_985.B11, COMP_2629.2
NET_3511: COMP_992.B11, COMP_2625.2
NET_3512: COMP_992.T11, COMP_2624.2
NET_3513: COMP_984.T11, COMP_2620.2
NET_3514: COMP_984.B11, COMP_2621.2
NET_3515: COMP_993.B11, COMP_2617.2
NET_3516: COMP_993.T11, COMP_2616.2
NET_3517: COMP_994.T11, COMP_2612.2
NET_3518: COMP_994.B11, COMP_2613.2
NET_3519: COMP_995.B11, COMP_2609.2
NET_3520: COMP_995.T11, COMP_2608.2
NET_3521: COMP_996.T11, COMP_2604.2
NET_3522: COMP_996.B11, COMP_2605.2
NET_3523: COMP_997.B11, COMP_2601.2
NET_3524: COMP_997.T11, COMP_2600.2
NET_3525: COMP_998.T11, COMP_2596.2
NET_3526: COMP_998.B11, COMP_2597.2
NET_3527: COMP_999.B11, COMP_2593.2
NET_3528: COMP_999.T11, COMP_2592.2
NET_3565: COMP_988.T12, COMP_2642.2
NET_3566: COMP_988.B12, COMP_2643.2
NET_3567: COMP_989.B12, COMP_2639.2
NET_3568: COMP_989.T12, COMP_2638.2
NET_3569: COMP_990.T12, COMP_2634.2
NET_3570: COMP_990.B12, COMP_2635.2
NET_3571: COMP_991.B12, COMP_2631.2
NET_3572: COMP_991.T12, COMP_2630.2
NET_3573: COMP_985.T12, COMP_2626.2
NET_3574: COMP_985.B12, COMP_2627.2
NET_3575: COMP_992.B12, COMP_2623.2
NET_3576: COMP_992.T12, COMP_2622.2
NET_3577: COMP_984.T12, COMP_2618.2
NET_3578: COMP_984.B12, COMP_2619.2
NET_3579: COMP_993.B12, COMP_2615.2
NET_3580: COMP_993.T12, COMP_2614.2
NET_3581: COMP_994.T12, COMP_2610.2
NET_3582: COMP_994.B12, COMP_2611.2
NET_3583: COMP_995.B12, COMP_2607.2
NET_3584: COMP_995.T12, COMP_2606.2
NET_3585: COMP_996.T12, COMP_2602.2
NET_3586: COMP_996.B12, COMP_2603.2
NET_3587: COMP_997.B12, COMP_2599.2
NET_3588: COMP_997.T12, COMP_2598.2
NET_3589: COMP_998.T12, COMP_2594.2
NET_3590: COMP_998.B12, COMP_2595.2
NET_3591: COMP_999.B12, COMP_2591.2
NET_3592: COMP_999.T12, COMP_2590.2

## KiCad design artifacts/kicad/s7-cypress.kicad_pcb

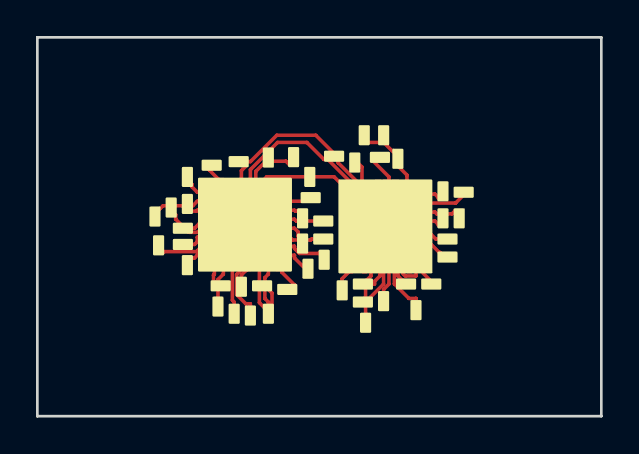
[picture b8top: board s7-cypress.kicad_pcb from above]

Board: 2 copper layers, 31.3 x 21.0 mm, 50 parts (0 on the bottom side), 43 nets.

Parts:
C106: C106
C107: C107
C463: C463
C464: C464
R231: R231
R234: R234
R235: R235
R236: R236
R237: R237
R239: R239
R249: R249
R250: R250
R743: R743
R744: R744
R834: R834
R842: R842
R843: R843
R918: R918
R919: R919
R920: R920
R921: R921
R922: R922
R923: R923
R924: R924
R925: R925
R926: R926
R927: R927
R928: R928
R929: R929
R930: R930
R931: R931
R932: R932
R1017: R1017
R1018: R1018
R1060: R1060
R1061: R1061
R1062: R1062
R1063: R1063
R1064: R1064
R1065: R1065
R1066: R1066
R1067: R1067
R1238: R1238
R1239: R1239
R1240: R1240
R1241: R1241
R1242: R1242
R1365: R1365
U59: U59
U100: U100

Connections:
AD_GPIO_EXP_HALFA: R234.0, U59.2
AD_GPIO_EXP_HALFB: R231.1, U100.2
GP_ASIC1_STRAP_FLASH_PRSNT_GPIO_EXP: R1238.1, U59.3
GP_ASIC2_STRAP_FLASH_PRSNT_GPIO_EXP: R1239.1, U59.4
GP_ASIC_SOC_JTAG_BUF_EN_L_R: R1242.1, U100.3
GP_GPIO_EXP_RESET_L_R: R237.1, R239.1, U59.5, U100.4
GP_SPI_ASIC1_FW_BUF1_EN_L_R: R249.1, U100.5
GP_SPI_ASIC2_FW_BUF1_EN_L_R: R250.1, U100.6
GP_SW_I2C_MUXS_SEL_A_R: R743.1, U100.7
GP_SW_I2C_MUXS_SEL_B_R: R744.1, U100.8
I2C_TESTING_GPIO_SCL: R235.1, U59.6, U100.9
I2C_TESTING_GPIO_SDA: R236.1, U59.7, U100.10
S_1V8_CPLD_IO_EN_R: R1067.1, U59.9
S_1V8_QPS_EN_GPIO_EXP: R1365.1, U100.22
S_3V3_ASIC_EN_R: R1064.1, U59.10
S_3V3_CTRL_PWR_EN_R: R834.1, U59.11
S_3V3_OSC1_EN_R: R1062.1, U59.12
S_3V3_OSC2_EN_R: R1063.1, U59.13
S_5V_CLK1_EN_R: R1065.1, U59.14
S_5V_CLK2_EN_R: R1066.1, U59.15
S_ASIC1_RST_L_R: R1017.1, U59.16
S_ASIC1_TCXO_EN_R: R1241.1, U100.23
S_ASIC2_RST_L_R: R1018.1, U59.17
S_ASIC2_TCXO_EN_R: R1240.1, U100.24
S_CLK_BRD1_OE_L_R: R931.1, U100.25
S_CLK_BRD1_PROGRAM_EN_L_R: R928.1, U100.26
S_CLK_BRD1_PWR_EN_R: R842.1, U100.27
S_CLK_BRD2_OE_L_R: R932.1, U100.28
S_CLK_BRD2_PROGRAM_EN_L_R: R929.1, U100.29
S_CLK_BRD2_PWR_EN_R: R843.1, U100.30
S_DVDD_S0_ASIC1_EN_R: R921.1, U59.18
S_DVDD_S0_ASIC2_EN_R: R926.1, U59.19
S_DVDD_S1_ASIC1_EN_R: R922.1, U59.20
S_DVDD_S1_ASIC2_EN_R: R927.1, U59.21
S_HVDD_S0_ASIC1_EN_R: R919.1, U59.22
S_HVDD_S0_ASIC2_EN_R: R924.1, U59.23
S_HVDD_S1_ASIC1_EN_R: R920.1, U59.24
S_HVDD_S1_ASIC2_EN_R: R925.1, U59.25
S_MAIL_BOX_I2C_EN_GPIO_EXP_L: R930.0, U59.26
S_VDD_ASIC1_EN_R: R918.1, U59.27
S_VDD_ASIC2_EN_R: R923.1, U59.28
S_VDRV1_EN_R: R1060.1, U59.29
S_VDRV2_EN_R: R1061.1, U59.30
